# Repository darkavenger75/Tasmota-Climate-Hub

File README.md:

Seeed Xiao ESP32-C6 based climate controller for Tasmota

A flexible Tasmota hub with 4 sensor inputs and 5 relay outputs. Can replace your collection of timer switches and thermostats (e.g. fish tank, terrarium) to allow for more complex control and the ability to check/change settings via the web interface. This is a stand-alone device not requiring internet access or any external controller/hub. Being based on Tasmota it can be integrated into e.g. Home Assistant. 
- RJ9 inputs for Sonoff WTS01 or THS01 (or whatever you want to connect requiring 1 GPIO, GND, 3.3V).
- Solid state relay main voltage outputs, max. 2A each.
- Option to add Zigbee module Ebyte E18-MS1 to integrate some of your Zigbee devices (check https://zigbee.blakadder.com/zigbee2tasmota.html for compatibility).

Instructions
- Eagle schematic, board, Gerber, BOM and CPL files are provided. Someone like JLCPCB can make the PCB and assemble it for you (check placement of components!). You might have to preorder the RJ9 sockets and solid state relays (Omron or Panasonic) or add them later yourself.
- The unit has an integrated power supply. There is mains voltage on the board, do not fry yourself!
- Flash with Tasmota for ESP32C6. If you want Zigbee support you must compile your own version, e.g. with Gitpod.
- Set-up GPIO according to "Tasmota_ESP32C6_GPIO_Config.png" and your own configuration.
- If attaching DS18x20 close the jumpers on the respective ports to add pullup resistors.
- If attaching THS01 (SI7021) add rule "ON System#Init DO DhtDelay 480,40 ENDON" or sensor might not work reliably.
- If you want the Zigbee module you have to flash it first with Z-Stack Home 1.2 coordinator firmware from https://github.com/Koenkk/Z-Stack-firmware. A debug port is provided. See https://tasmota.github.io/docs/CC2530/#flash-zigbee-adapter for options. Do not forget to close the jumper next to the board such that it will be powered.
- An example rule with 6 timers (3x ON/OFF) set to "rule" is provided. It will switch relays 1 and 2 on and off according to timers 1/2 and 3/4. It will switch relay 3 according to the temperture input from DS18B20 with limits chosen by timer 3 from mem1/mem2 (timer on) or mem3/mem4 (timer off). Unlike using the timers directly to switch the relays this rule sets the outputs correctly after restarting the device.
- I recommend to use the autoexec.be in the Berry folder instead of using rules.

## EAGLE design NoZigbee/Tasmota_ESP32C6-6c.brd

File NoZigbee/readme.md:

A different version of the Tasmota hub without Zigbee, with only 3 inputs but 6 relays, including a conventional 5A one (on GPIO23).
Can be squeezed into a Tru Components F1 TC-6649500 case together with 5 - 6 AS 45081 power sockets and a C-14 mains connector.
Or use a smaller 3D printed shell (3DShell_Tasmota_ESP32C6-6c.zip) together with Wieland GST18 i3 connectors.

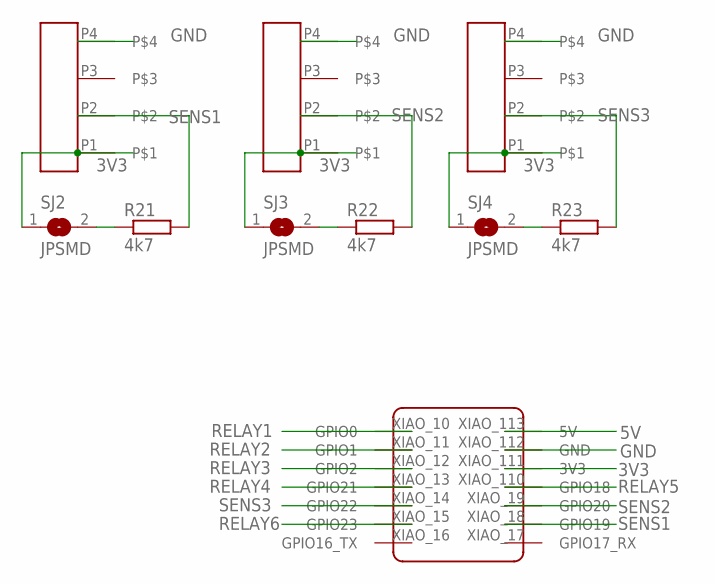
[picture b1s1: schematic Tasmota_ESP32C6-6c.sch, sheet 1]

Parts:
R21, R22, R23: 4k7; R0805
SENSOR1, SENSOR2, SENSOR3: GMX-N-44; GMX-N-4
SJ2, SJ3, SJ4: JPSMD; SJ
U$1: 1x7P; XIAO_ESP32C6

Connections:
3V3: SENSOR1.P1, SENSOR2.P1, SENSOR3.P1, SJ2.1, SJ3.1, SJ4.1, U$1.XIAO_111 (3V3)
5V: U$1.XIAO_113 (5V); also elsewhere on the board
GND: SENSOR1.P4, SENSOR2.P4, SENSOR3.P4, U$1.XIAO_112 (GND); also elsewhere on the board
unnamed: R21.1, SJ2.2
unnamed: R22.1, SJ3.2
unnamed: R23.1, SJ4.2
RELAY1: U$1.XIAO_10 (GPIO0); also elsewhere on the board
RELAY2: U$1.XIAO_11 (GPIO1); also elsewhere on the board
RELAY3: U$1.XIAO_12 (GPIO2); also elsewhere on the board
RELAY4: U$1.XIAO_13 (GPIO21); also elsewhere on the board
RELAY5: U$1.XIAO_110 (GPIO18); also elsewhere on the board
RELAY6: U$1.XIAO_15 (GPIO23); also elsewhere on the board
SENS1: R21.2, SENSOR1.P2, U$1.XIAO_18 (GPIO19)
SENS2: R22.2, SENSOR2.P2, U$1.XIAO_19 (GPIO20)
SENS3: R23.2, SENSOR3.P2, U$1.XIAO_14 (GPIO22)

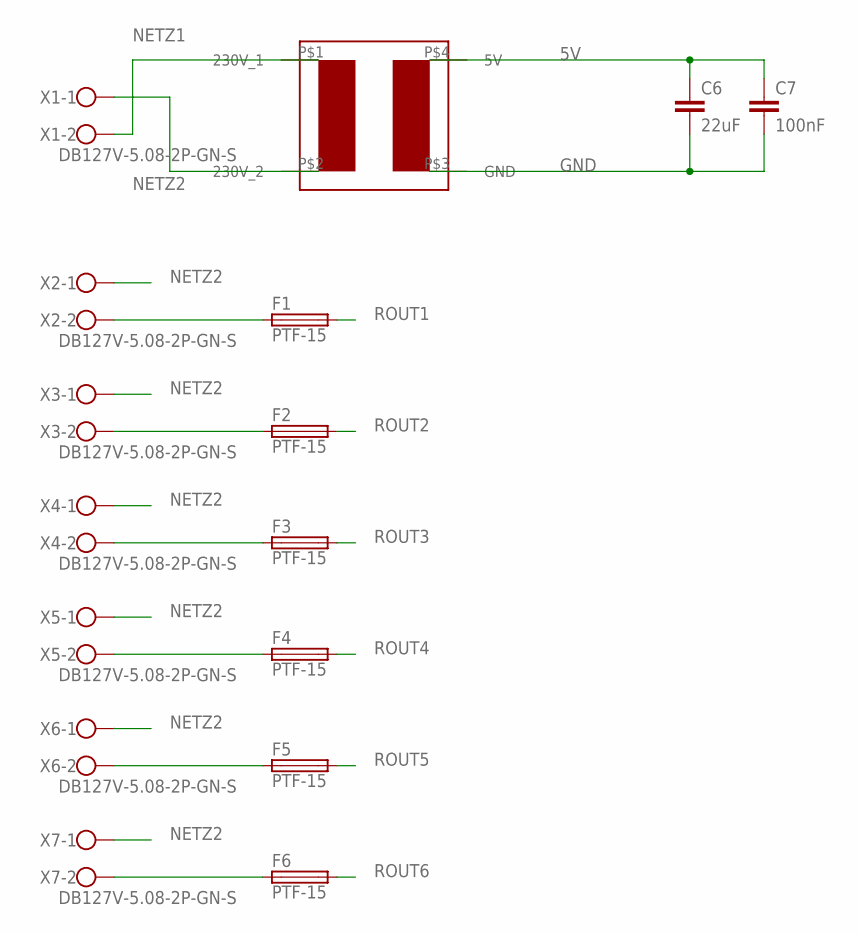
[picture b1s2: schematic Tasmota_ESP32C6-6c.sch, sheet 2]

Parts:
C6: 22uF; C0805
C7: 100nF; C0805
F1, F2, F3, F4, F5, F6: PTF-15; SH22,5
U$3: HAW3-220S05T2
X1, X2, X3, X4, X5, X6, X7: DB127V-5.08-2P-GN-S; W237-102

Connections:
5V: C6.1, C7.1, U$3.P$4 (5V); also elsewhere on the board
GND: C6.2, C7.2, U$3.P$3 (GND); also elsewhere on the board
unnamed: F1.1, X2.2
unnamed: F2.1, X3.2
unnamed: F3.1, X4.2
unnamed: F4.1, X5.2
unnamed: F5.1, X6.2
unnamed: F6.1, X7.2
NETZ1: U$3.P$1 (230V_1), X1.2; also elsewhere on the board
NETZ2: U$3.P$2 (230V_2), X1.1, X2.1, X3.1, X4.1, X5.1, X6.1, X7.1
ROUT1: F1.2; also elsewhere on the board
ROUT2: F2.2; also elsewhere on the board
ROUT3: F3.2; also elsewhere on the board
ROUT4: F4.2; also elsewhere on the board
ROUT5: F5.2; also elsewhere on the board
ROUT6: F6.2; also elsewhere on the board

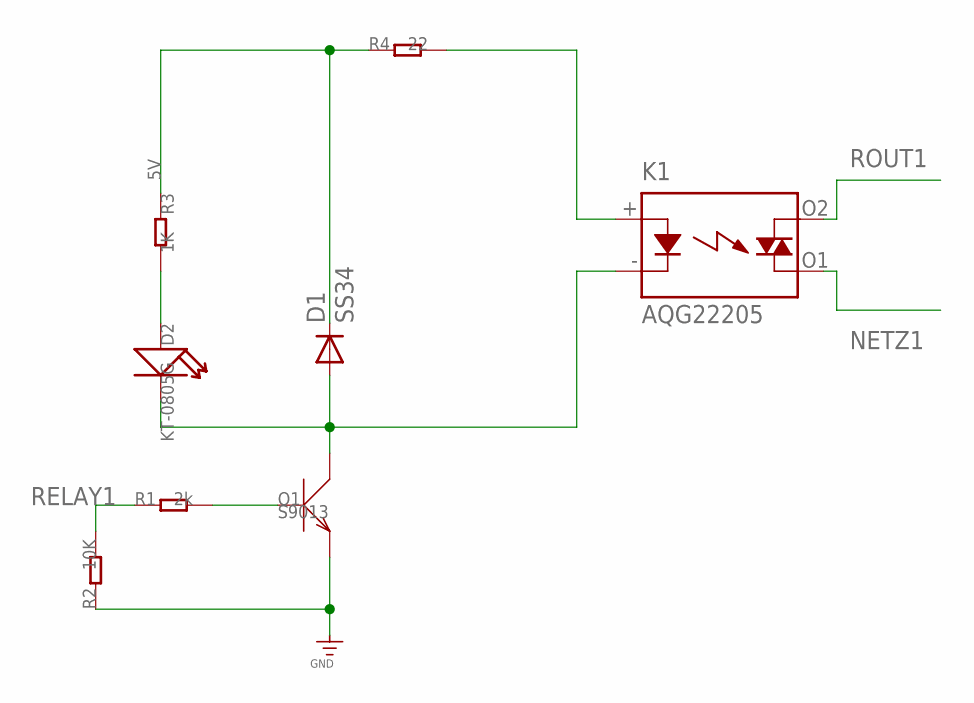
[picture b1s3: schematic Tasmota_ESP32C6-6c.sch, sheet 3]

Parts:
D1: SS34; DO-214AC
D2: KT-0805G; LED-0805
K1: AQG22205; AQG
Q1: S9013; SOT23
R1: 2k; R0805
R2: 10K; R0805
R3: 1K; R0805
R4: 22; R0805

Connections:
5V: D1.C, R3.1, R4.1; also elsewhere on the board
GND: Q1.2 (E), R2.1; also elsewhere on the board
unnamed: Q1.1 (B), R1.2
unnamed: D1.A, D2.-, K1.- (K), Q1.3 (C)
unnamed: D2.+, R3.2
unnamed: K1.+ (A), R4.2
NETZ1: K1.O1 (DS2); also elsewhere on the board
RELAY1: R1.1, R2.2; also elsewhere on the board
ROUT1: K1.O2 (DS1); also elsewhere on the board

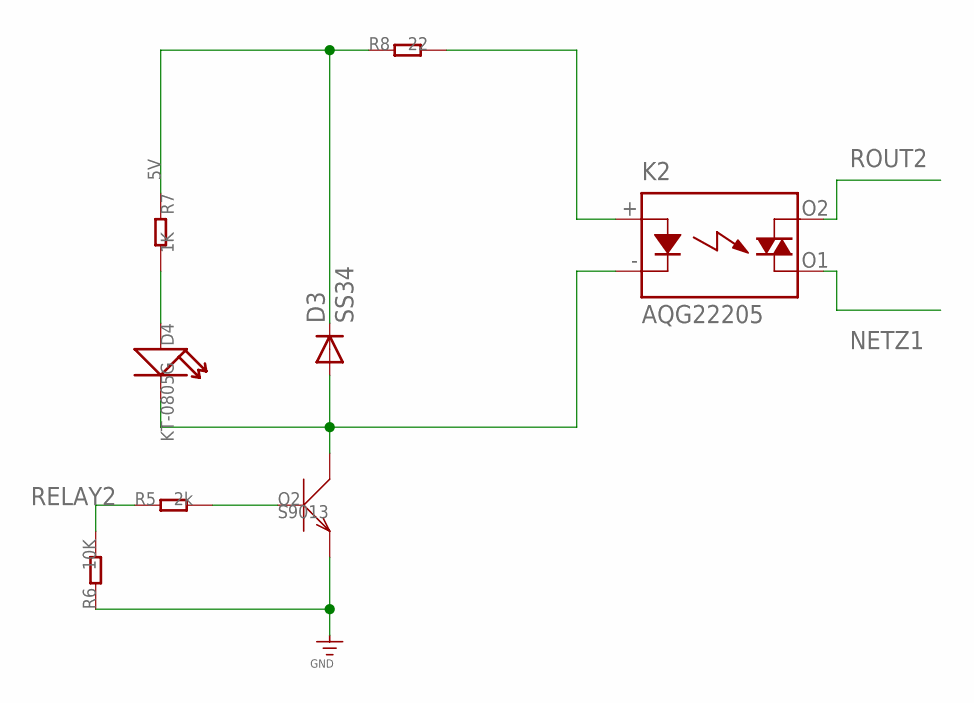
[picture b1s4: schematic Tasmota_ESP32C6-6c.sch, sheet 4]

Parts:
D3: SS34; DO-214AC
D4: KT-0805G; LED-0805
K2: AQG22205; AQG
Q2: S9013; SOT23
R5: 2k; R0805
R6: 10K; R0805
R7: 1K; R0805
R8: 22; R0805

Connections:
5V: D3.C, R7.1, R8.1; also elsewhere on the board
GND: Q2.2 (E), R6.1; also elsewhere on the board
unnamed: Q2.1 (B), R5.2
unnamed: D3.A, D4.-, K2.- (K), Q2.3 (C)
unnamed: D4.+, R7.2
unnamed: K2.+ (A), R8.2
NETZ1: K2.O1 (DS2); also elsewhere on the board
RELAY2: R5.1, R6.2; also elsewhere on the board
ROUT2: K2.O2 (DS1); also elsewhere on the board

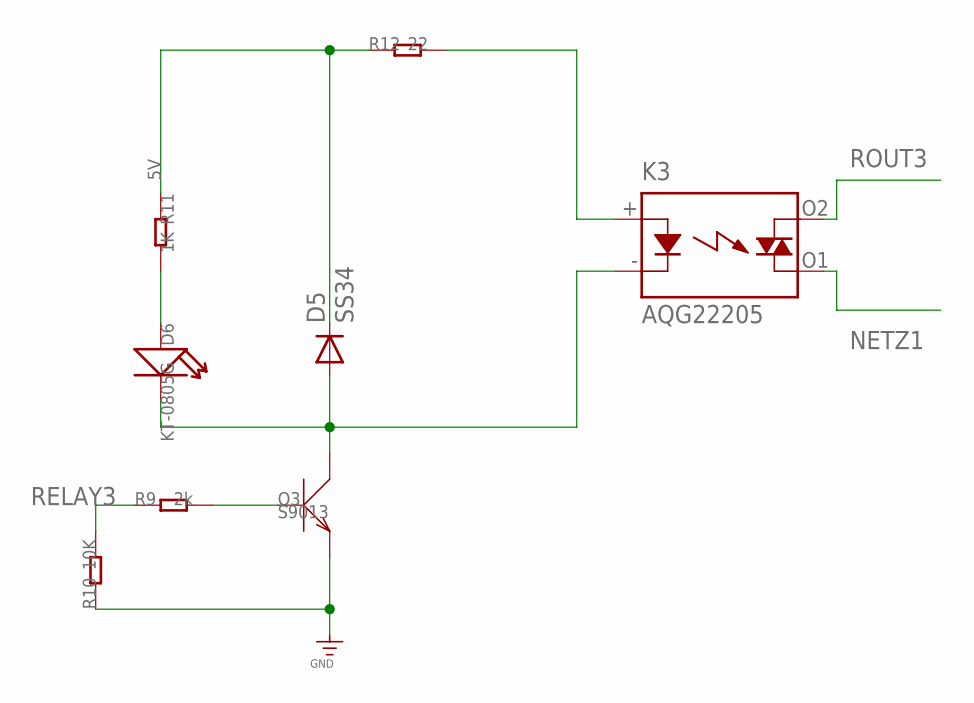
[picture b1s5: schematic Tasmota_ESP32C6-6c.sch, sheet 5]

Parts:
D5: SS34; DO-214AC
D6: KT-0805G; LED-0805
K3: AQG22205; AQG
Q3: S9013; SOT23
R9: 2k; R0805
R10: 10K; R0805
R11: 1K; R0805
R12: 22; R0805

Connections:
5V: D5.C, R11.1, R12.1; also elsewhere on the board
GND: Q3.2 (E), R10.1; also elsewhere on the board
unnamed: Q3.1 (B), R9.2
unnamed: D5.A, D6.-, K3.- (K), Q3.3 (C)
unnamed: D6.+, R11.2
unnamed: K3.+ (A), R12.2
NETZ1: K3.O1 (DS2); also elsewhere on the board
RELAY3: R9.1, R10.2; also elsewhere on the board
ROUT3: K3.O2 (DS1); also elsewhere on the board

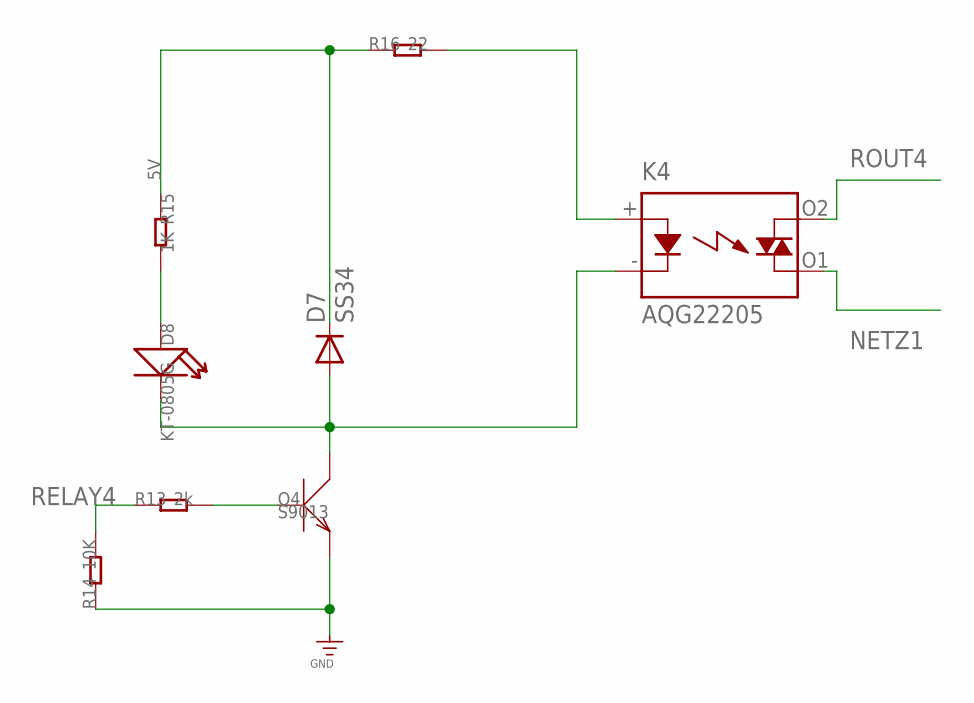
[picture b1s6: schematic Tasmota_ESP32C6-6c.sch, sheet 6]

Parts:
D7: SS34; DO-214AC
D8: KT-0805G; LED-0805
K4: AQG22205; AQG
Q4: S9013; SOT23
R13: 2k; R0805
R14: 10K; R0805
R15: 1K; R0805
R16: 22; R0805

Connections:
5V: D7.C, R15.1, R16.1; also elsewhere on the board
GND: Q4.2 (E), R14.1; also elsewhere on the board
unnamed: Q4.1 (B), R13.2
unnamed: D7.A, D8.-, K4.- (K), Q4.3 (C)
unnamed: D8.+, R15.2
unnamed: K4.+ (A), R16.2
NETZ1: K4.O1 (DS2); also elsewhere on the board
RELAY4: R13.1, R14.2; also elsewhere on the board
ROUT4: K4.O2 (DS1); also elsewhere on the board

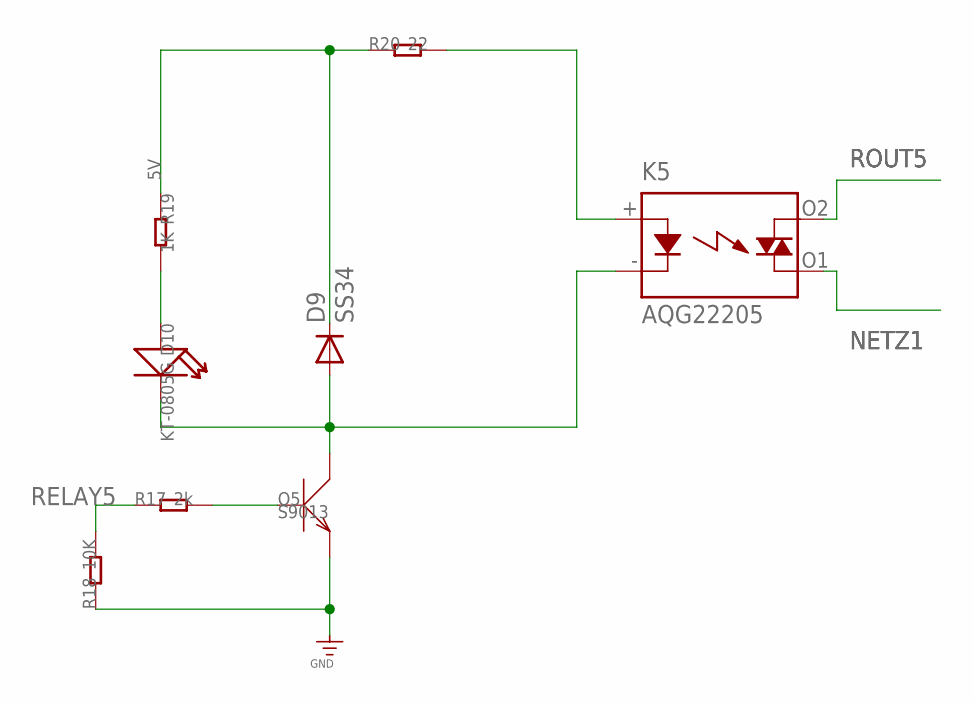
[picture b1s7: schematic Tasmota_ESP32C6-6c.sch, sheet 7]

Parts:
D9: SS34; DO-214AC
D10: KT-0805G; LED-0805
K5: AQG22205; AQG
Q5: S9013; SOT23
R17: 2k; R0805
R18: 10K; R0805
R19: 1K; R0805
R20: 22; R0805

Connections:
5V: D9.C, R19.1, R20.1; also elsewhere on the board
GND: Q5.2 (E), R18.1; also elsewhere on the board
unnamed: Q5.1 (B), R17.2
unnamed: D10.+, R19.2
unnamed: K5.+ (A), R20.2
unnamed: D9.A, D10.-, K5.- (K), Q5.3 (C)
NETZ1: K5.O1 (DS2); also elsewhere on the board
RELAY5: R17.1, R18.2; also elsewhere on the board
ROUT5: K5.O2 (DS1); also elsewhere on the board

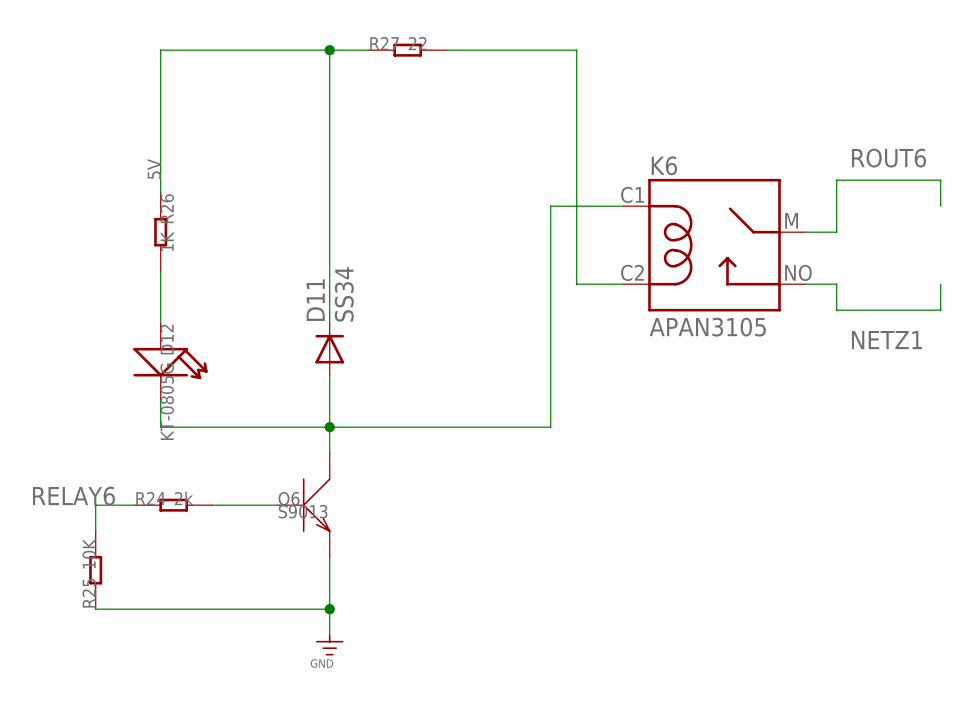
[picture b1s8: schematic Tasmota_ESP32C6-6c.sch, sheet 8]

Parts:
D11: SS34; DO-214AC
D12: KT-0805G; LED-0805
K6: APAN3105; RELAY_APAN3105
Q6: S9013; SOT23
R24: 2k; R0805
R25: 10K; R0805
R26: 1K; R0805
R27: 22; R0805

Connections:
5V: D11.C, R26.1, R27.1; also elsewhere on the board
GND: Q6.2 (E), R25.1; also elsewhere on the board
unnamed: Q6.1 (B), R24.2
unnamed: D11.A, D12.-, K6.C1, Q6.3 (C)
unnamed: D12.+, R26.2
unnamed: K6.C2, R27.2
NETZ1: K6.NO; also elsewhere on the board
RELAY6: R24.1, R25.2; also elsewhere on the board
ROUT6: K6.M; also elsewhere on the board

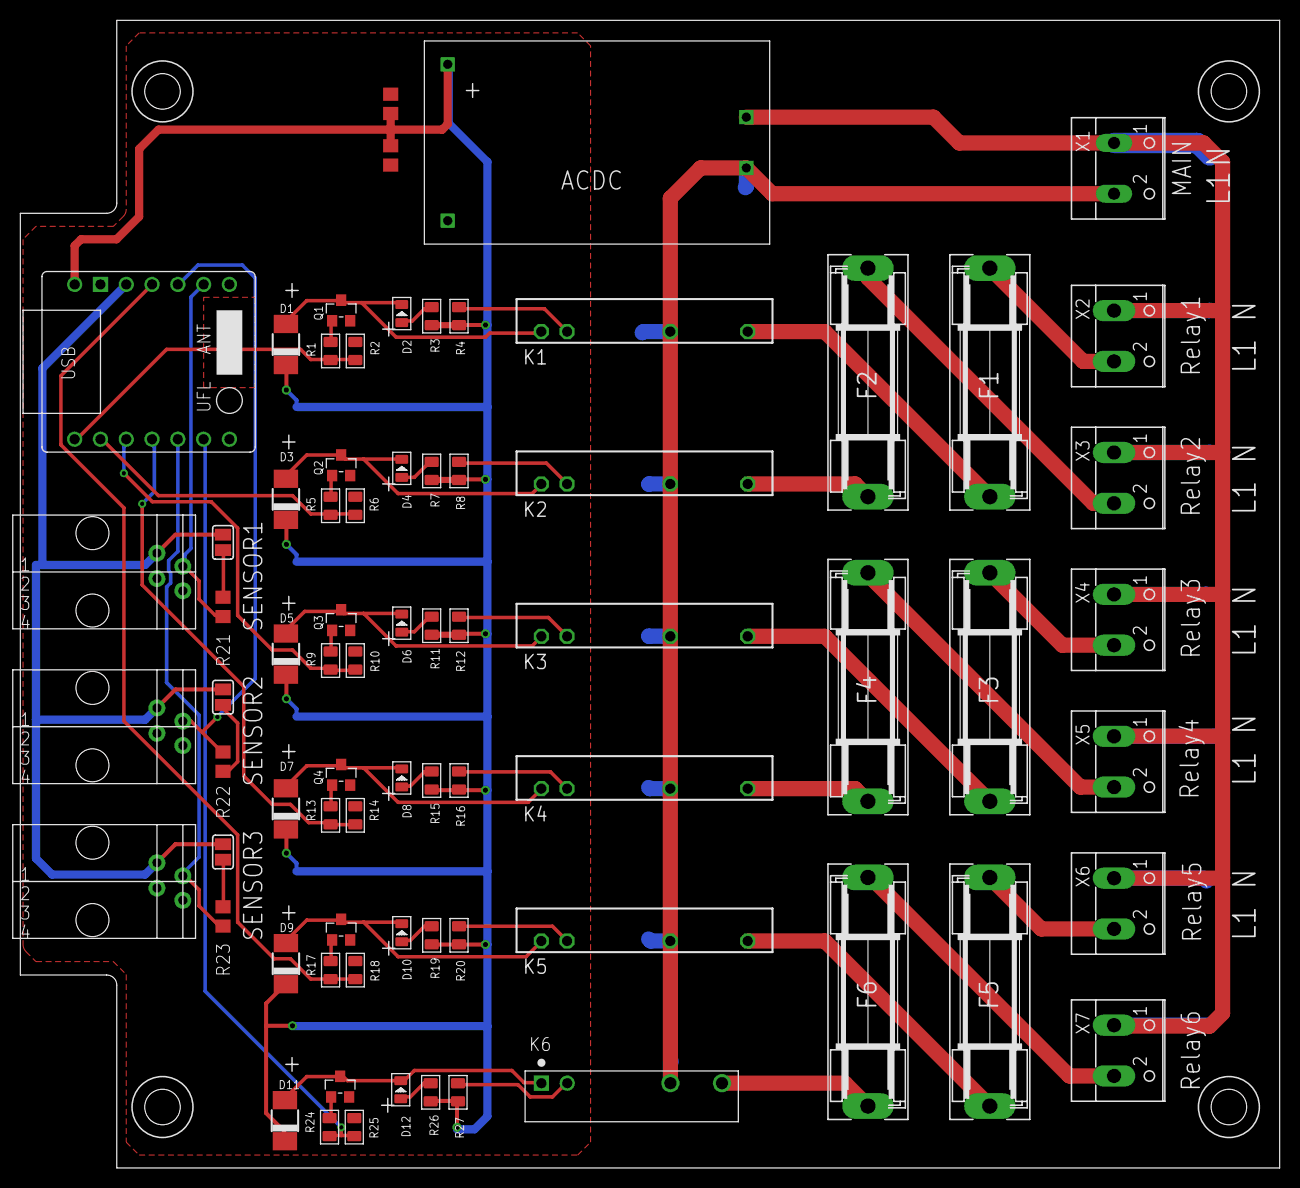
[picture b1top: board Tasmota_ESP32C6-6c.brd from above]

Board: 2 copper layers, 124.0 x 113.0 mm, 74 parts (0 on the bottom side), 53 nets.

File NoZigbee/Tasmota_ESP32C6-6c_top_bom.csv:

Comment,Designator,Footprint,LCSC Part #
1K,R3 R7 R11 R15 R19 R26,R0805,
1x7P,U$1,XIAO_ESP32C6,C2832270,
1x7P,U$1b,XIAO_ESP32C6,C2832270,
2k,R1 R5 R9 R13 R17 R24,R0805,
4k7,R21 R22 R23,R0805,
10K,R2 R6 R10 R14 R18 R25,R0805,
22,R4 R8 R12 R16 R20 R27,R0805,
22uF,C6,C0805,
100nF,C7,C0805,
APAN3105,K6,RELAY_APAN3105,
AQG22205,K1 K2 K3 K4 K5,AQG,
DB127V-5.08-2P-GN-S,X1 X2 X3 X4 X5 X6 X7,W237-102,
GMX-N-44,SENSOR1 SENSOR2 SENSOR3,GMX-N-4,
HAW3-220S05T2,U$3,HAW3-220S05T2,
KT-0805G,D2 D4 D6 D8 D10 D12,LED-0805,
PTF-15,F1,SH22 5,
PTF-15,F2,SH22 5,
PTF-15,F3,SH22 5,
PTF-15,F4,SH22 5,
PTF-15,F5,SH22 5,
PTF-15,F6,SH22 5,
S9013,Q1 Q2 Q3 Q4 Q5 Q6,SOT23,
SS34,D1 D3 D5 D7 D9 D11,DO-214AC,
